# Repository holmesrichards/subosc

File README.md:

# subosc
Kosmo or Eurorack format sub oscillator 

Circuit design by Analog Lab Swiss (Carmelo Azarello).

PCB and Kosmo front panel design by Rich Holmes.

Zener diodes on the sub oscillator output are optional and probably don't really do anything. They can be omitted. Zeners on the clock div outputs limit those outputs to 5.1V and should be included.

Kosmo panel is for a dual sub oscillator module. It uses two copies of the PCB. In one of the two, omit the Clock Div output jacks, resistors, and diodes. Also omit the power header, series Schottky diode, and 10uF capacitor; instead run wires from the +12V and ground wire pads on the first board to the corresponding pads on the second.

A version was built and tested and found to work once I corrected my mistake (by a factor of 1000) in the value of C1. That value has been updated here, so all should be good. (I used a ceramic cap but have specified poly box. Either should be okay but poly may be better.)

For Azarello's version this is taken from, see https://www.facebook.com/photo.php?fbid=10158135029647692&set=pcb.10157466790532753&type=3&theater . Some minor differences:
* Original was battery powered, with 100 µF cap to ground
* Original C1 was specified as ceramic
* Original had 47 µF cap on input, described as optional
* Original used 2n3904 for Q1

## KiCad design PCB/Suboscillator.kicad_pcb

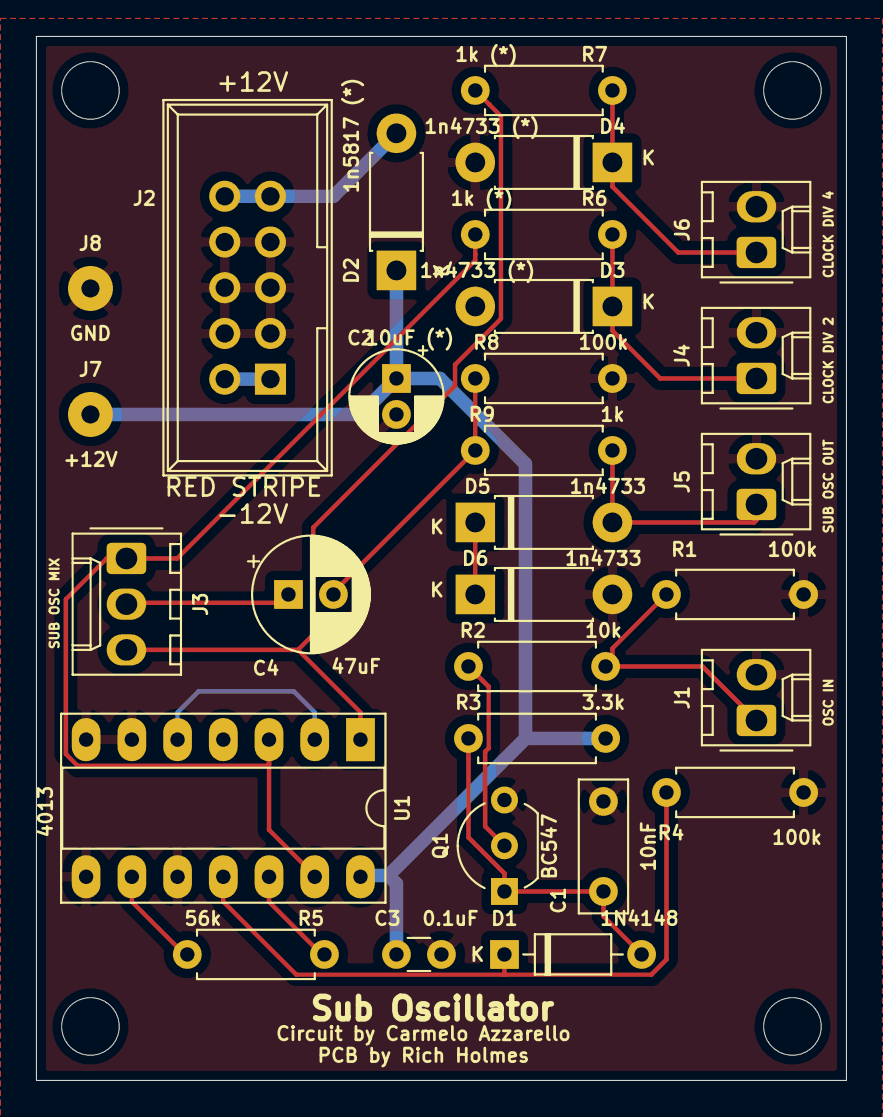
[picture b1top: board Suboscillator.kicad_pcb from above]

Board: 2 copper layers, 45.0 x 58.0 mm, 29 parts (0 on the bottom side), 19 nets.

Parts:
C1: 10nF; C_Rect_L7.2mm_W2.5mm_P5.00mm_FKS2_FKP2_MKS2_MKP2
C2: 10uF (*); CP_Radial_D5.0mm_P2.00mm
C3: 0.1uF; C_Disc_D3.0mm_W1.6mm_P2.50mm
C4: 47uF; CP_Radial_D6.3mm_P2.50mm
D1: 1N4148; D_DO-35_SOD27_P7.62mm_Horizontal
D2: 1n5817 (*); D_DO-41_SOD81_P7.62mm_Horizontal
D3, D4: 1n4733 (*); D_DO-41_SOD81_P7.62mm_Horizontal
D5, D6: 1n4733; D_DO-41_SOD81_P7.62mm_Horizontal
J1, J5: 2 PIN HDR; Molex_KK-254_AE-6410-02A_1x02_P2.54mm_Vertical
J2: EURO_PWR_2x5 (*); Power_Header
J3: 3 PIN HDR; Molex_KK-254_AE-6410-03A_1x03_P2.54mm_Vertical
J4, J6: 2 PIN HDR (*); Molex_KK-254_AE-6410-02A_1x02_P2.54mm_Vertical
J7, J8: Wire pad; SolderWirePad_1x01_Drill1mm
Q1: BC547; TO-92_Inline_Wide
R1, R4, R8: 100k; R_Axial_DIN0207_L6.3mm_D2.5mm_P7.62mm_Horizontal
R2: 10k; R_Axial_DIN0207_L6.3mm_D2.5mm_P7.62mm_Horizontal
R3: 3.3k; R_Axial_DIN0207_L6.3mm_D2.5mm_P7.62mm_Horizontal
R5: 56k; R_Axial_DIN0207_L6.3mm_D2.5mm_P7.62mm_Horizontal
R6, R7: 1k (*); R_Axial_DIN0207_L6.3mm_D2.5mm_P7.62mm_Horizontal
R9: 1k; R_Axial_DIN0207_L6.3mm_D2.5mm_P7.62mm_Horizontal
U1: 4013; DIP-14_W7.62mm_Socket_LongPads

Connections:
+12V: C2.1, C3.1, D2.1, J7.1, R3.1, U1.14
/-1_OCT: J3.1, R6.2, U1.3, U1.13
/-2_OCT: J3.3, R7.2, U1.1
/SUB_OSC_MIX: C4.1, J3.2
GND: C1.2, C2.2, C3.2, D3.2, D4.2, D6.2, J1.2, J2.3, J2.4, J2.5, J2.6, J2.7, J2.8, J4.2, J5.2, J6.2, J8.1, Q1.3, R1.2, R4.2, R8.2, U1.6, U1.7, U1.8, U1.10
unnamed: C1.1, D1.2, Q1.1, R3.2
unnamed: C4.2, R8.1, R9.2
unnamed: D1.1, R4.1, U1.11
unnamed: D2.2, J2.9, J2.10
unnamed: D3.1, J4.1, R6.1
unnamed: D4.1, J6.1, R7.1
unnamed: D5.1, D6.1
unnamed: D5.2, J5.1, R9.1
unnamed: J1.1, R1.1, R2.2
unnamed: J2.1, J2.2
unnamed: Q1.2, R2.1
unnamed: R5.1, U1.12
unnamed: R5.2, U1.9
unnamed: U1.2, U1.5

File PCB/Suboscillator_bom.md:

# Suboscillator BOM

Sun 05 Jul 2020 09:53:15 AM EDT

Generated from schematic by Eeschema 5.1.5-52549c5~84~ubuntu18.04.1

**Component Count:** 34

| Value | Qty | Part | Description | Vendor |
| ----- | --- | ---- | ----------- | ------ |
| C1, C2 | 2 | 10uF | Polarized capacitor |  |
| C3 | 1 | 0.1uF | Unpolarized capacitor |  |
| C4 | 1 | 47uF | Polarized capacitor |  |
| D1 | 1 | 1N4148 | 100V 0.15A standard switching diode, DO-35 |  |
| D2 | 1 | 1n5817 | Schottky diode |  |
| D3, D4, D5, D6 | 4 | 1n4733 | Zener diode |  |
| J1, J4, J5, J6 | 4 | Molex_KK-254_AE-6410-02A | Generic connector, single row, 01x02, script generated (kicad-library-utils/schlib/autogen/connector/) |  |
| J2 | 1 | EURO_PWR_2x5 |  |  |
| J3 | 1 | Molex_KK-254_AE-6410-03A | Generic connector, single row, 01x03, script generated (kicad-library-utils/schlib/autogen/connector/) |  |
| J7, J8 | 2 | Wire pad | Generic connector, single row, 01x01, script generated (kicad-library-utils/schlib/autogen/connector/) |  |
| J9, J10, J11, J12 | 4 | 1/4" Jack | Audio Jack, 2 Poles (Mono / TS) |  |
| Q1 | 1 | BC547 | 0.1A Ic, 45V Vce, Small Signal NPN Transistor, TO-92 |  |
| R1, R4, R8 | 3 | 100k | Resistor |  |
| R2 | 1 | 10k | Resistor |  |
| R3 | 1 | 3.3k | Resistor |  |
| R5 | 1 | 56k | Resistor |  |
| R6, R7, R9 | 3 | 1k | Resistor |  |
| RV1 | 1 | B100k | Potentiometer |  |
| U1 | 1 | 4013 | Dual D  FlipFlop, Set & reset |  |

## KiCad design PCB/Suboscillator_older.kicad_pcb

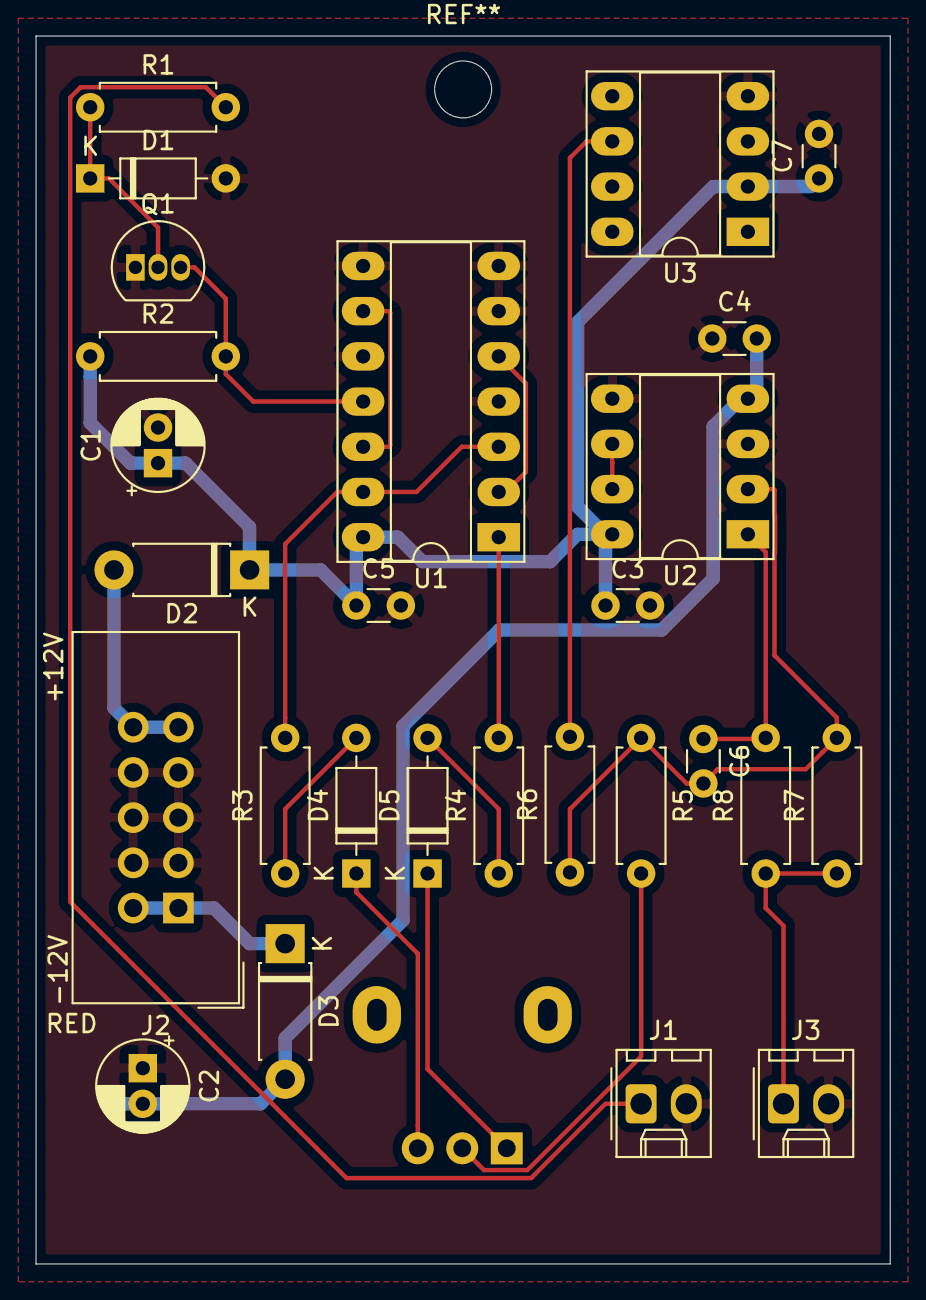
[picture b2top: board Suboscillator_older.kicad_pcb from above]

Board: 2 copper layers, 48.0 x 69.0 mm, 28 parts (1 on the bottom side), 22 nets.

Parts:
C1, C2: 10uF; CP_Radial_D5.0mm_P2.00mm
C3, C4, C5, C7: 0.1uF; C_Disc_D3.0mm_W1.6mm_P2.50mm
C6: 47pF; C_Disc_D3.0mm_W1.6mm_P2.50mm
D1, D4, D5: 1N4148; D_DO-35_SOD27_P7.62mm_Horizontal
D2, D3: D_Schottky; D_DO-41_SOD81_P7.62mm_Horizontal
J1: Conn_01x02 Osc In; Molex_KK-254_AE-6410-02A_1x02_P2.54mm_Vertical
J2: EURO_PWR_2x5; IDC-Header_2x05_P2.54mm_Vertical
J3: Conn_01x02 Sub Osc Out; Molex_KK-254_AE-6410-02A_1x02_P2.54mm_Vertical
Q1: 2N3904; TO-92_Inline
R1, R3, R4: 47k; R_Axial_DIN0207_L6.3mm_D2.5mm_P7.62mm_Horizontal
R2: 68k; R_Axial_DIN0207_L6.3mm_D2.5mm_P7.62mm_Horizontal
R5: 120k; R_Axial_DIN0207_L6.3mm_D2.5mm_P7.62mm_Horizontal
R6, R7: 100k; R_Axial_DIN0207_L6.3mm_D2.5mm_P7.62mm_Horizontal
R8: 330R; R_Axial_DIN0207_L6.3mm_D2.5mm_P7.62mm_Horizontal
RV1: 100k MIX; Potentiometer_Alpha_RD901F-40-00D_Single_Vertical
U1: 4013; DIP-14_W7.62mm_Socket_LongPads
U2: TL072; DIP-8_W7.62mm_Socket_LongPads
U3: REF02CP+; DIP-8_W7.62mm_Socket_LongPads

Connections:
+12V: C1.1, C3.1, C5.1, C7.1, D2.1, R2.1, U1.14, U2.8, U3.2
-12V: C2.2, C4.2, D3.2, U2.4
/-1_OCT: R3.2, U1.3, U1.13
/-2_OCT: R4.2, U1.1
/MIX: R5.2, RV1.2
GND: C1.2, C2.1, C3.2, C4.1, C5.2, C7.2, D1.2, J1.2, J2.3, J2.4, J2.5, J2.6, J2.7, J2.8, J3.2, Q1.1, U1.4, U1.6, U1.7, U1.8, U1.10, U2.3, U2.5, U3.4
unnamed: C6.1, R8.2, U2.1
unnamed: C6.2, R5.1, R6.1, R7.2, U2.2
unnamed: D1.1, Q1.2, R1.1
unnamed: D2.2, J2.9, J2.10
unnamed: D3.1, J2.1, J2.2
unnamed: D4.1, RV1.3
unnamed: D4.2, R3.1
unnamed: D5.1, RV1.1
unnamed: D5.2, R4.1
unnamed: Q1.3, R2.2, U1.11
unnamed: U1.2, U1.5
unnamed: U1.9, U1.12
unnamed: U2.6, U2.7
OSC_INPUT: J1.1, R1.2
REF: R6.2, U3.6
SUB_OSC_OUT: J3.1, R7.1, R8.1

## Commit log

2020-07-05 Initial version
2020-07-05 Update LICENSE
2020-07-05 rm older version
2020-07-05 rm unused footprint library
2020-07-05 Add panel components
2020-07-06 Comments in schematic and README
2020-09-01 Schematics cleanup
2020-09-27 Schematic pdf, footprint, and 10nF, 10uF, what's the difference?
2020-09-28 Correct C1
2020-09-28 C1 disc to box
2020-09-28 Link to and comparison with Azarello's original.
2020-09-28 2 Zeners are optional
2021-01-02 Footprints updated
2021-01-17 Include lib table files
